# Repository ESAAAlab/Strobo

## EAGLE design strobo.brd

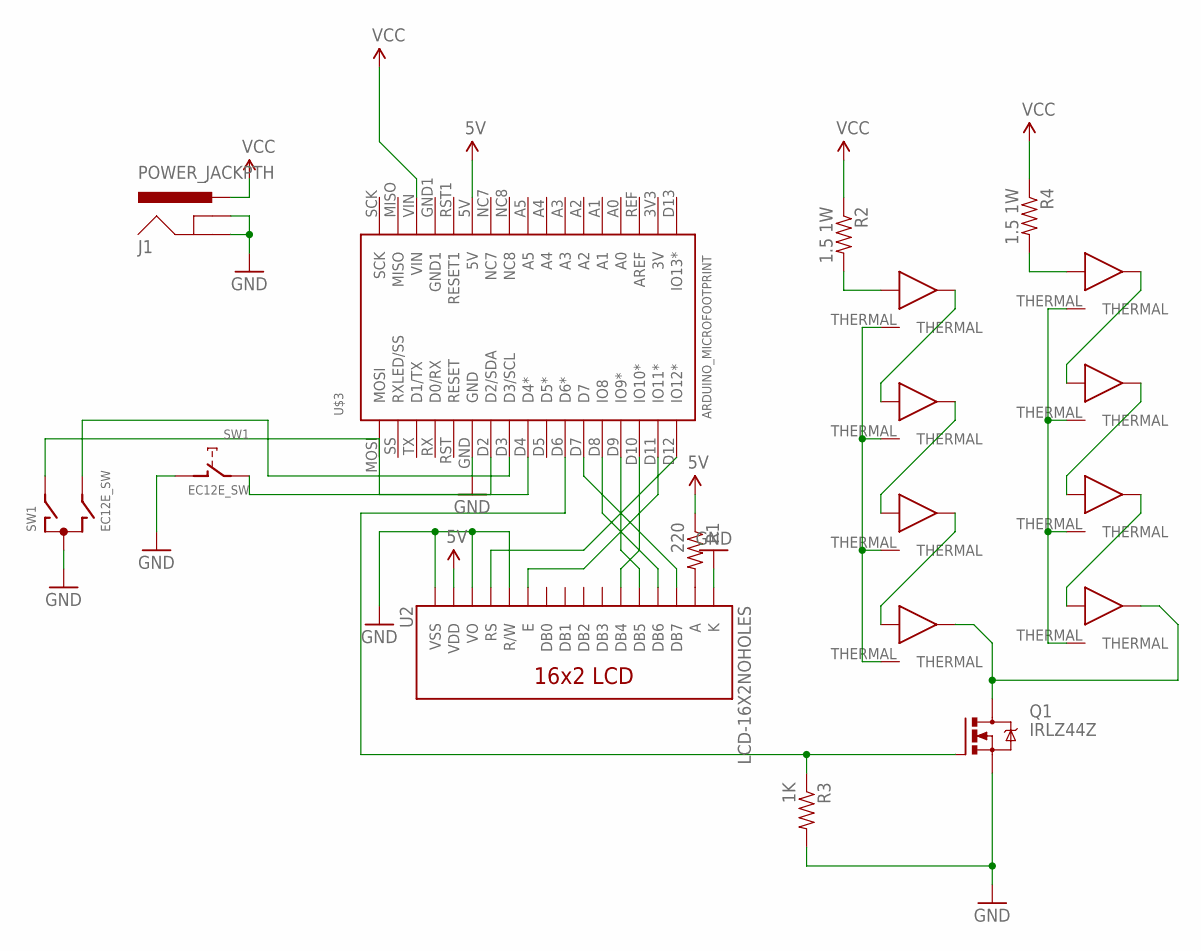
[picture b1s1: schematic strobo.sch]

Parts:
J1: POWER_JACKPTH; POWER_JACK_PTH
Q1: IRLZ44Z; TO220BH
R1: 220; AXIAL-0.4
R2, R4: 1.5 1W; AXIAL-0.4
R3: 1K; AXIAL-0.4
SW1: EC12E_SW; ALPS_EC12E_SW
U2: LCD-16X2NOHOLES; LCD-16X2_NOHOLES
U$1, U$2, U$4, U$5, U$6, U$7, U$8, U$9: LED; LUXEONREBEL
U$3: ARDUINO_MICROFOOTPRINT; ARDUINO-MICRO

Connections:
5V: R1.P$1 (1), U2.2 (VDD), U$3.5V
GND: J1.GND, J1.GNDBREAK, Q1.S, R3.P$2 (2), SW1.C, SW1.D (1), U2.1 (VSS), U2.3 (VO), U2.5 (R/W), U2.16 (K), U$3.GND
unnamed: U2.14 (DB7), U$3.D7
unnamed: U2.13 (DB6), U$3.D8 (IO8)
unnamed: U2.12 (DB5), U$3.D9 (IO9*)
unnamed: U2.11 (DB4), U$3.D10 (IO10*)
unnamed: U2.6 (E), U$3.D11 (IO11*)
unnamed: U2.4 (RS), U$3.D12 (IO12*)
unnamed: R2.P$2 (2), U$1.ANODE
unnamed: R1.P$2 (2), U2.15 (A)
unnamed: U$4.CATHODE, U$5.ANODE
unnamed: U$2.CATHODE, U$4.ANODE
unnamed: U$1.CATHODE, U$2.ANODE
unnamed: Q1.G, R3.P$1 (1), U$3.D6 (D6*)
unnamed: SW1.E (2), U$3.D4 (D4*)
unnamed: SW1.A, U$3.D2 (D2/SDA)
unnamed: SW1.B, U$3.D3 (D3/SCL)
unnamed: U$8.CATHODE, U$9.ANODE
unnamed: U$7.CATHODE, U$8.ANODE
unnamed: U$6.CATHODE, U$7.ANODE
unnamed: R4.P$2 (2), U$6.ANODE
unnamed: Q1.D, U$5.CATHODE, U$9.CATHODE
THERMAL1: U$1.THERMAL, U$2.THERMAL, U$4.THERMAL, U$5.THERMAL
THERMAL2: U$6.THERMAL, U$7.THERMAL, U$8.THERMAL, U$9.THERMAL
VCC: J1.PWR, R2.P$1 (1), R4.P$1 (1), U$3.VIN

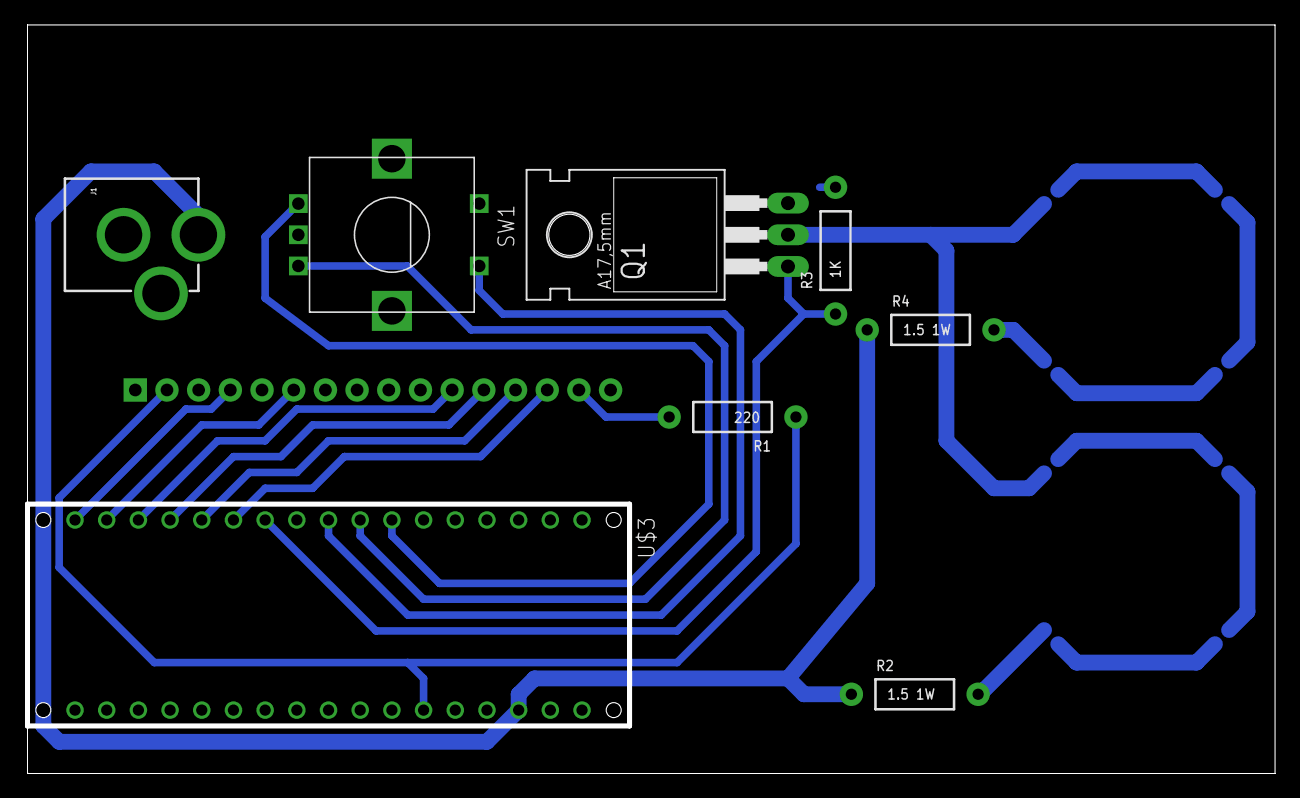
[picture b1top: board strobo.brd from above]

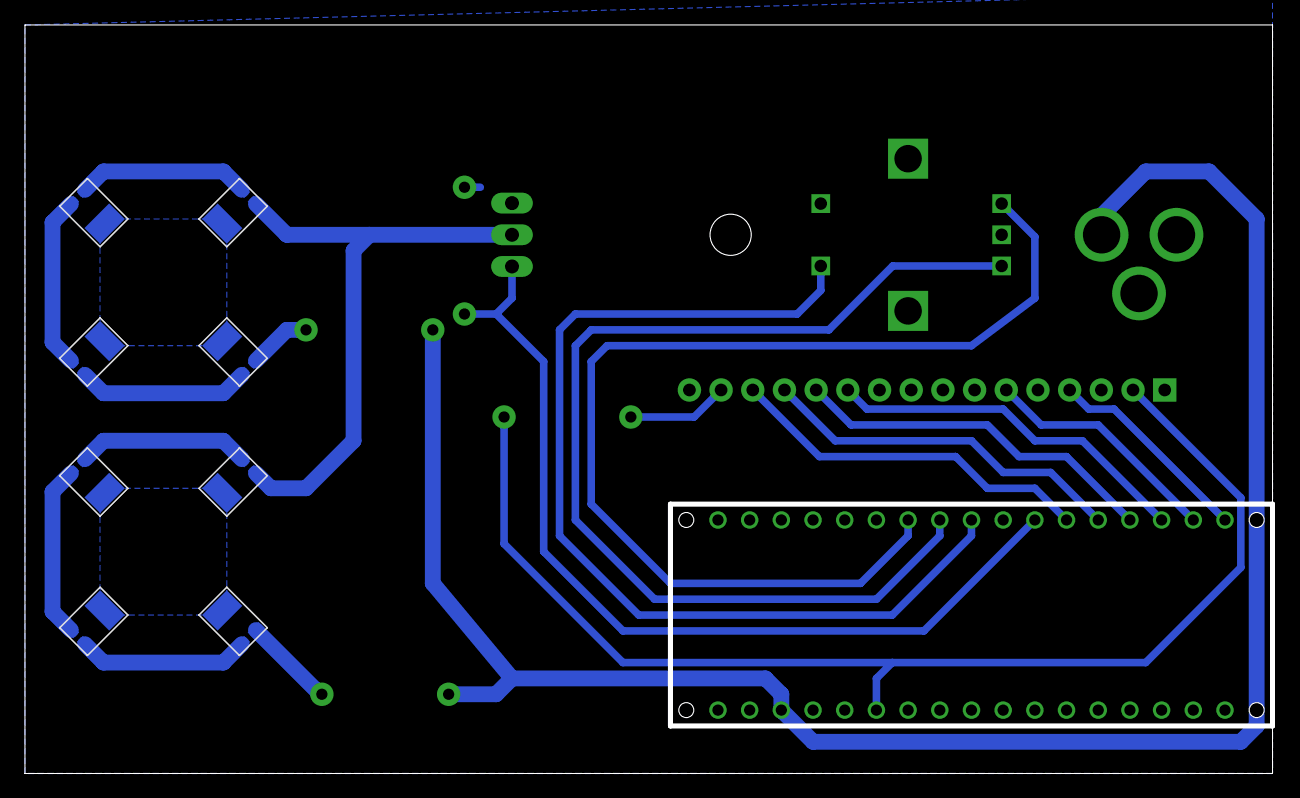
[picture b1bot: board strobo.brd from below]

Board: 2 copper layers, 99.8 x 59.6 mm, 17 parts (8 on the bottom side), 25 nets.

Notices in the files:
parts and their libraries:
SparkFun-Resistors: Licensing: CC v3.0 Share-Alike You are welcome to use this library for commercial purposes.
